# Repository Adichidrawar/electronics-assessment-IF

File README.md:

# Electronics Assessment IF

This repository contains two KiCad-based electronics design projects for an IMU and ESP32-based hardware assessment. The work is organized into two PCB design folders with schematic, layout, CSV data, and manufacturing output files.

## Project Overview

The assessment includes:
- An ESP32-oriented board design in the esp32_project folder
- A second IMU-focused board design in the imu_design folder
- Generated Gerber files for fabrication review
- Project metadata and design exports for documentation and handoff
- The solution for Part 2 — Analog front end is provided in the PDF named Part 2 — Analog front end SOLUTIONS.pdf

## Repository Structure

```text
.
├── README.md
├── esp32_project/
│   ├── esp32_project.kicad_pro
│   ├── esp32_project.kicad_sch
│   ├── esp32_project.kicad_pcb
│   ├── ESP_For_IMU.csv
│   ├── freerouting.dsn
│   ├── Gerber_files/
│   └── report.txt
└── imu_design/
    ├── imu_design.kicad_pro
    ├── imu_design.kicad_sch
    ├── imu_design.kicad_pcb
    ├── ESP_For_IMU.csv
    ├── gerber_files/
    └── imu_design.pdf
```

## Architecture and block diagram

A simple view of the intended system is:

```text
IMU sensor board ---> 300 mm cable ---> ESP32 host board ---> USB/serial or wireless link
      |                                |
      |                                +--> debug UART / status LEDs
      +--> power and ground return ---+
```

The architecture is intentionally simple:
1. The IMU board collects motion data from the sensor.
2. That data is transferred to the ESP32 board over a short, controlled digital link.
3. The ESP32 board handles communication, buffering, and any downstream logging or wireless transmission.
4. The cable carries only the signals needed for reliable timing and low-noise transfer: power, ground, clock, chip-select, data in/out, and optionally an interrupt line.

## What crosses the 300 mm cable

I would keep the cable as a compact, low-noise digital link rather than trying to carry analog signals over a long run. In practice, the following would cross the 300 mm cable:
- 3.3 V power and ground
- SPI signals: SCLK, MOSI, MISO, CS
- Optionally an interrupt or data-ready line from the IMU to the host

Using SPI is the most practical choice because it is synchronous, relatively simple to debug, and is well suited to IMU register reads and burst transfers. I would not try to carry analog outputs or high-speed clocks over this cable unless the wiring is tightly controlled and shielded.

For a 300 mm cable, I would trust roughly 4 MHz SPI as a sensible starting point. 8 MHz is possible with good layout, controlled impedance, and proper grounding, but it is a stretch for a generic cable assembly. I would prefer 2 to 4 MHz for the first prototype and only raise it after validating signal integrity.

## How I would timestamp IMU samples

I would timestamp samples on the ESP32 side using a free-running hardware timer with microsecond resolution. The approach would be:
- Capture the current timer value immediately after the IMU interrupt or after the SPI transaction completes.
- Store that timestamp together with the received sample data.
- If possible, use the IMU data-ready interrupt to latch the time at the source rather than relying on a later software poll.

For a first-pass implementation, I would expect timing error on the order of tens of microseconds, roughly 10 to 50 microseconds, depending on SPI latency, interrupt handling, and scheduler jitter. That is usually good enough for slow-motion IMU logging, but it would not be suitable for very high-rate control loops without more careful real-time design.

## Component choices

The main parts would be:
- ESP32-WROOM-32 or similar ESP32 module: the main compute and communications hub, with enough GPIO and SPI capability for the IMU link.
- A 6-axis or 9-axis IMU such as ICM-42688 or MPU-6050: provides the motion sensing and a straightforward digital interface.
- A 3.3 V low-dropout regulator: keeps the logic rail stable and clean for the sensor and the ESP32.
- Decoupling capacitors and a small reset/boot network: these are essential for reliable startup and noise immunity.
- ESD and filtering parts on the cable side: helpful for protecting the board and reducing transient noise when the cable is moved or connected.

## Rough power budget

A realistic rough budget for a simple prototype is:
- ESP32 active: about 200 to 300 mA at 3.3 V
- IMU sensor: about 1 to 3 mA
- LDO and small support circuitry: a few milliamps

That gives a total active load of roughly 0.3 to 0.8 W, depending on Wi-Fi or Bluetooth activity. For a safe design margin, I would plan for a 3.3 V supply that can comfortably deliver at least 500 mA and preferably 1 A if the ESP32 is doing wireless work.

## What is most likely to be wrong

The three biggest risks on first bring-up are:
1. Cable or connector integrity: a poor ground return, bad pinout, or marginal connector contact can make SPI look flaky.
2. Power integrity: the 3.3 V rail may dip during startup or wireless bursts, causing resets or failed sensor reads.
3. Timing and signal quality: the IMU may fail to read correctly if the SPI clock is too fast or if the bus is not cleanly routed.

When the boards arrive, I would test in this order:
- Check the 3.3 V rail at the IMU and ESP32 pins under load.
- Verify continuity and ground return between the boards.
- Perform a simple SPI register read from the IMU using a known register value and confirm the response.
- Only then move to higher-rate logging or wireless transmit tests.

## What was not finished

The current design is a good starting point, but it is not yet a fully finished hardware package. The main unfinished items are:
- A formal BOM with exact part numbers and package sizes
- More careful connector and cable pinout documentation
- A bring-up checklist and test points for fast debugging

With another 3 hours, I would focus on:
- Completing the BOM and part references
- Adding test points for power, reset, SPI, and the IMU interrupt
- Writing a simple boot-and-read procedure so the first board bring-up is fast and repeatable

## How to open the designs

1. Install KiCad on your system.
2. Open the desired project folder.
3. Open the .kicad_pro file to load the full project in KiCad.
4. Review the schematic, PCB layout, and generated Gerber outputs.

## Notes

- The project folders already contain generated manufacturing outputs, making them suitable for review or fabrication preparation.
- The repository is intended for hardware design assessment documentation and version control of the PCB work.
- The report.txt file in the ESP32 project folder can be expanded with design notes, test results, or manufacturing comments as needed.

## Author

This repository was prepared as part of the electronics assessment for the IF hardware/mechatronics take-home task.

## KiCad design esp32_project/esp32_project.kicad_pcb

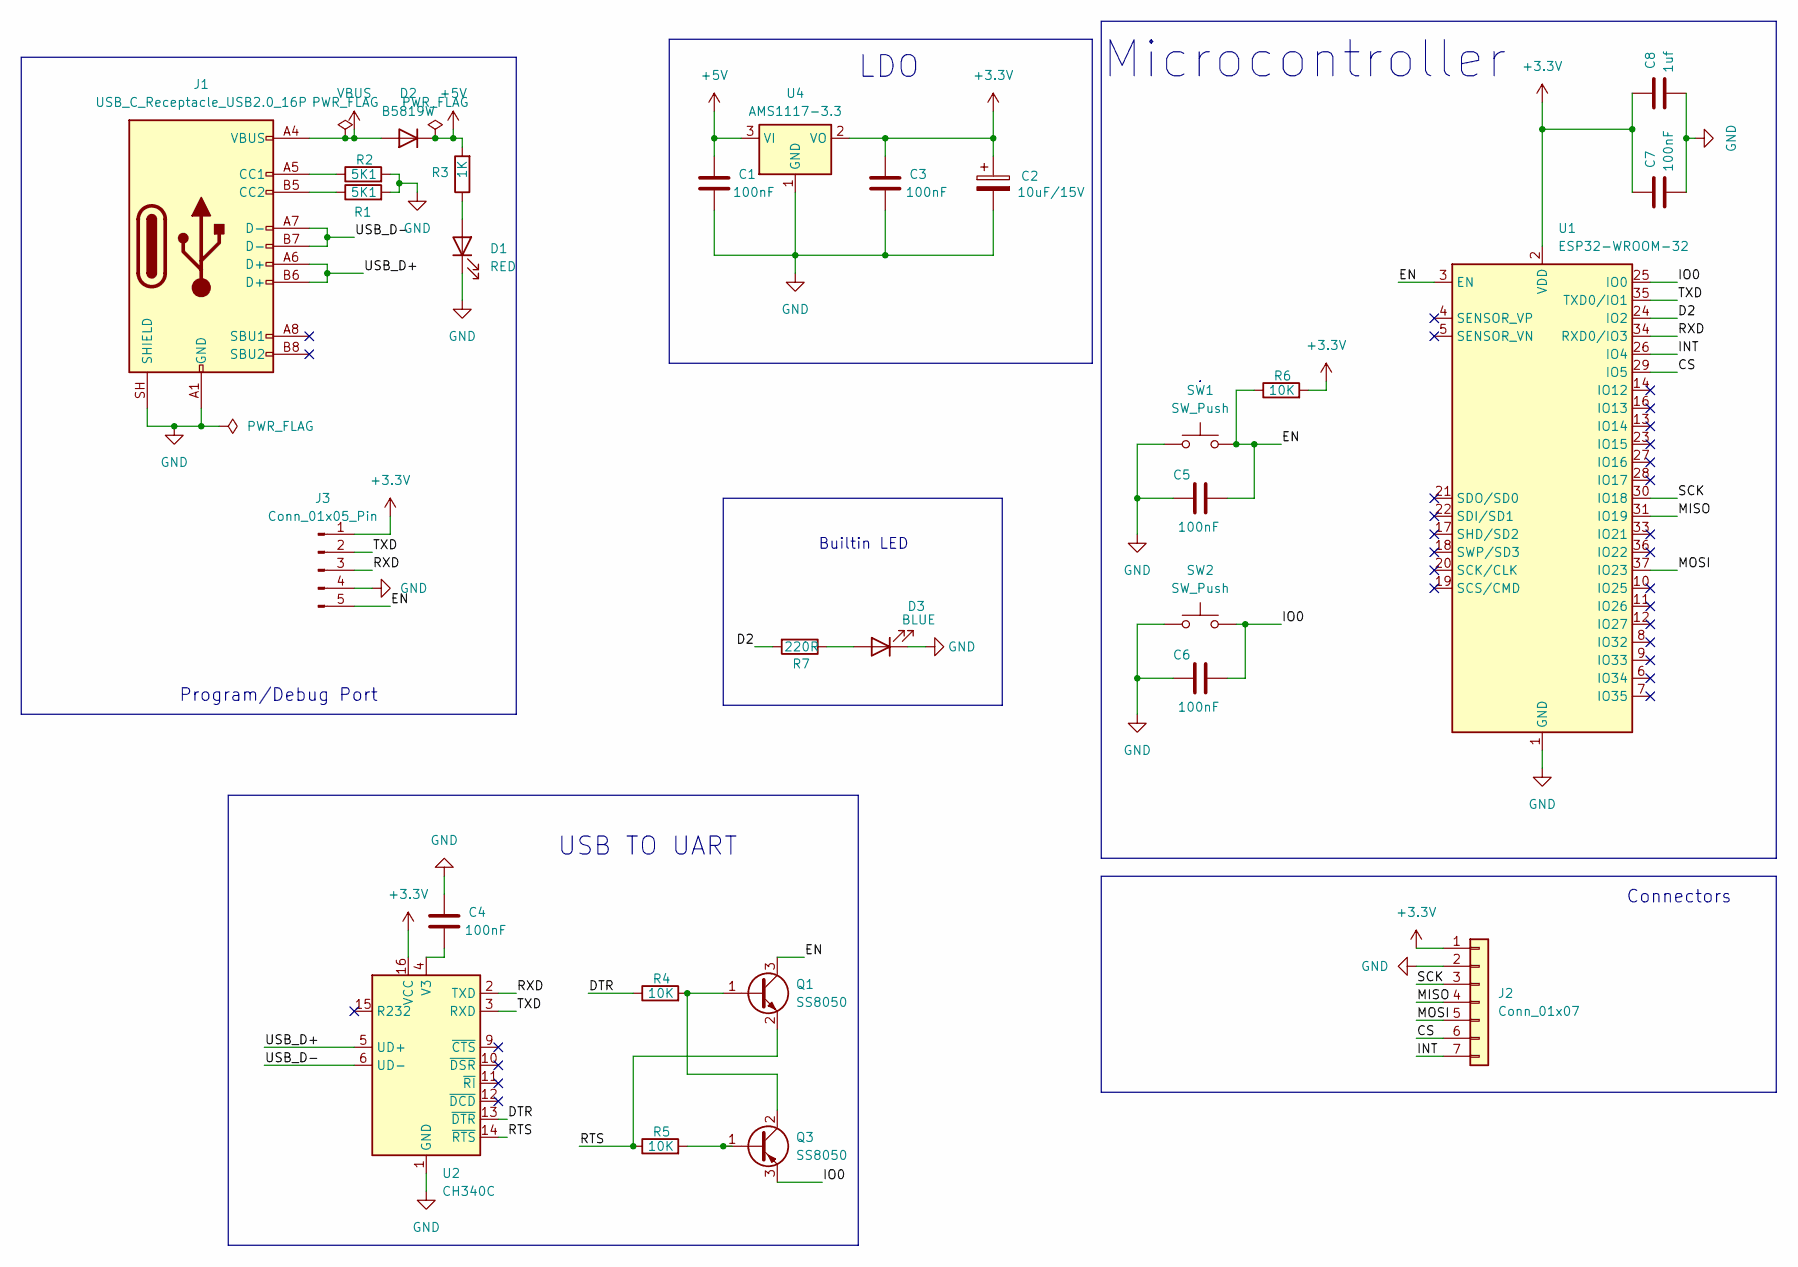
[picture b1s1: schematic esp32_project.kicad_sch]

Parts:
C1, C3, C4, C5, C6, C7: 100nF; C_0603_1608Metric
C2: 10uF/15V; CP_EIA-3216-10_Kemet-I_HandSolder
C8: 1uf; C_0603_1608Metric
D1: RED; LED_0603_1608Metric
D2: B5819W; D_SOD-123
D3: BLUE; LED_0603_1608Metric
J1: USB_C_Receptacle_USB2.0_16P; USB_C_Receptacle_HRO_TYPE-C-31-M-12
J2: Conn_01x07; JST_PH_B7B-PH-K_1x07_P2.00mm_Vertical
J3: Conn_01x05_Pin; PinHeader_1x06_P2.54mm_Vertical
Q1, Q3: SS8050; SOT-23
R1, R2: 5K1; R_0603_1608Metric
R3: 1K; R_0603_1608Metric
R4, R5, R6: 10K; R_0603_1608Metric
R7: 220R; R_0603_1608Metric
SW1, SW2: SW_Push; SW_Push_SPST_NO_Alps_SKRK
U1: ESP32-WROOM-32
U2: CH340C; SOIC-16_3.9x9.9mm_P1.27mm
U4: AMS1117-3.3; SOT-223-3_TabPin2

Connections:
+3.3V: C2.1, C3.1, C7.1, C8.1, J2.1, J3.1, R6.2, U1.2 (VDD), U2.16 (VCC), U4.2 (VO)
+5V: C1.1, D2.1 (K), R3.2, U4.3 (VI)
/CS: J2.6, U1.29 (IO5)
/D2: R7.2, U1.24 (IO2)
/DTR: R4.1, U2.13 (~DTR)
/EN: C5.2, J3.5, Q1.3 (C), R6.1, SW1.2, U1.3 (EN)
/INT: J2.7, U1.26 (IO4)
/IO0: C6.2, Q3.3 (E), SW2.2, U1.25 (IO0)
/MISO: J2.4, U1.31 (IO19)
/MOSI: J2.5, U1.37 (IO23)
/RTS: Q1.2 (E), R5.1, U2.14 (~RTS)
/RXD: J3.3, U1.34 (RXD0/IO3), U2.2 (TXD)
/SCK: J2.3, U1.30 (IO18)
/TXD: J3.2, U1.35 (TXD0/IO1), U2.3 (RXD)
/USB_D+: J1.A6 (D+), J1.B6 (D+), U2.5 (UD+)
/USB_D-: J1.A7 (D-), J1.B7 (D-), U2.6 (UD-)
GND: C1.2, C2.2, C3.2, C4.1, C5.1, C6.1, C7.2, C8.2, D1.1 (K), D3.1 (K), J1.A1 (GND), J1.A12 (GND), J1.B1 (GND), J1.B12 (GND), J1.SH (SHIELD), J2.2, J3.4, R1.2, R2.2, SW1.1, SW2.1, U1.1 (GND), U1.15 (GND), U1.38 (GND), U1.39 (GND), U2.1 (GND), U4.1 (GND)
unnamed: D1.2 (A), R3.1
unnamed: D3.2 (A), R7.1
unnamed: J1.A5 (CC1), R2.1
unnamed: J1.B5 (CC2), R1.1
unnamed: Q1.1 (B), Q3.2 (C), R4.2
unnamed: Q3.1 (B), R5.2
unnamed: C4.2, U2.4 (V3)
VBUS: D2.2 (A), J1.A4 (VBUS), J1.A9 (VBUS), J1.B4 (VBUS), J1.B9 (VBUS)

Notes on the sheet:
USB TO UART
Program/Debug Port
LDO
Microcontroller
Connectors
Builtin LED

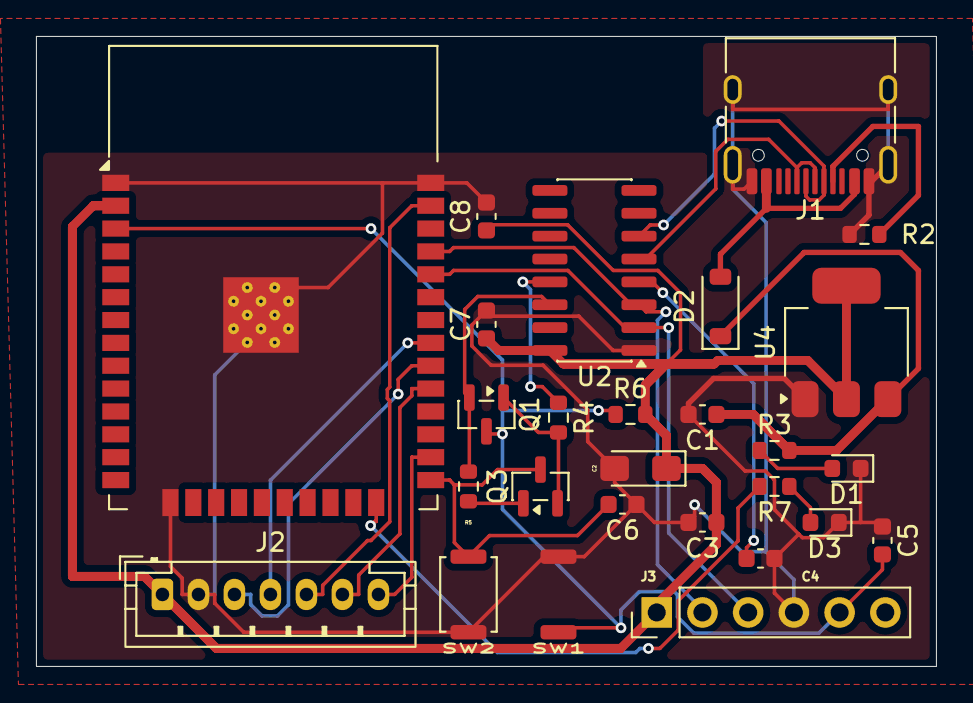
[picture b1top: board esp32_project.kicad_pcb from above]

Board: 2 copper layers, 50.0 x 35.0 mm, 27 parts (0 on the bottom side), 24 nets.

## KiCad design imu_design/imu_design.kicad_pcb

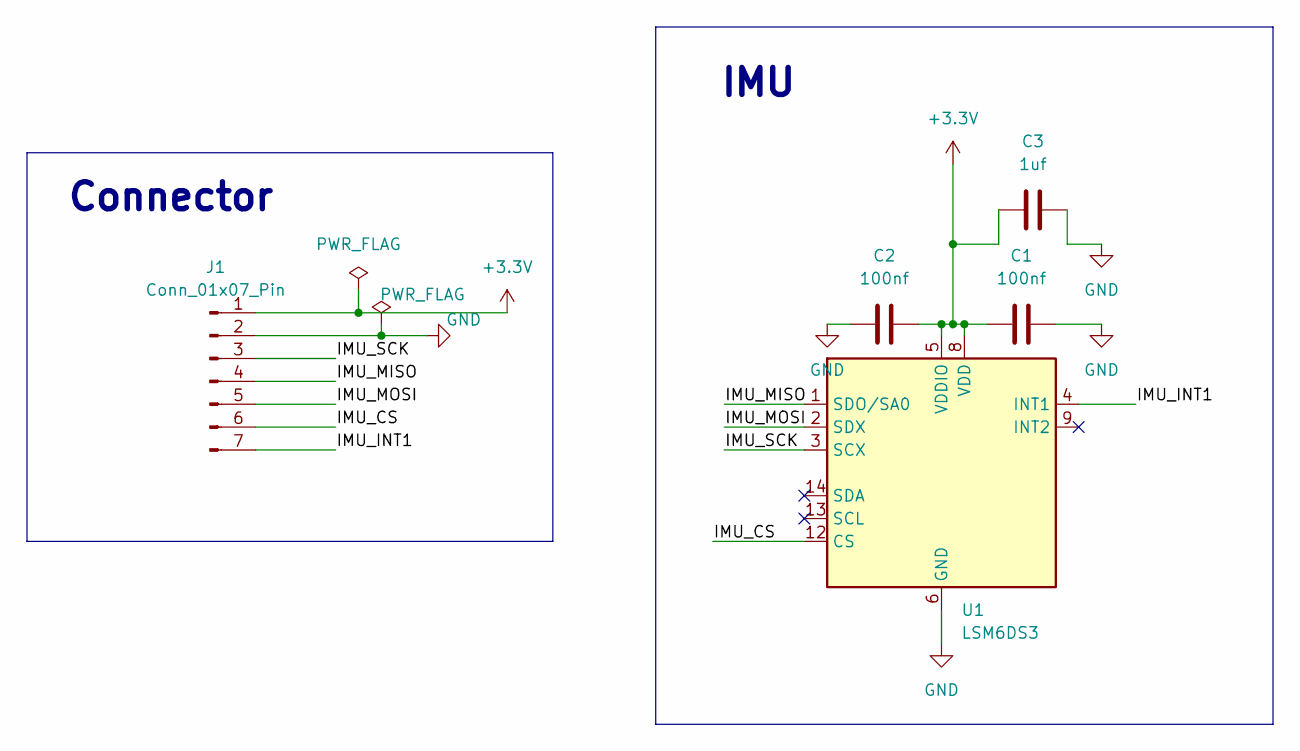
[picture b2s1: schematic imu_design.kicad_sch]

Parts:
C1, C2: 100nf; C_0603_1608Metric
C3: 1uf; C_0603_1608Metric
J1: Conn_01x07_Pin; JST_PH_B7B-PH-K_1x07_P2.00mm_Vertical
U1: LSM6DS3; LGA-14_3x2.5mm_P0.5mm_LayoutBorder3x4y

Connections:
+3.3V: C1.1, C2.2, C3.1, J1.1, U1.5 (VDDIO), U1.8 (VDD)
/IMU_CS: J1.6, U1.12 (CS)
/IMU_INT1: J1.7, U1.4 (INT1)
/IMU_MISO: J1.4, U1.1 (SDO/SA0)
/IMU_MOSI: J1.5, U1.2 (SDX)
/IMU_SCK: J1.3, U1.3 (SCX)
GND: C1.2, C2.1, C3.2, J1.2, U1.6 (GND), U1.7 (GND)

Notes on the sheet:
Connector
IMU

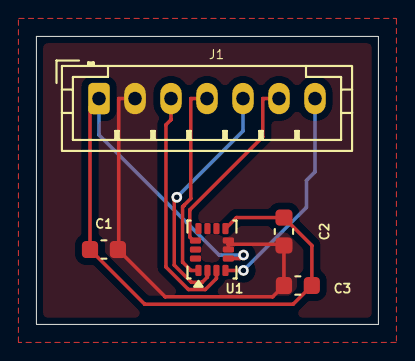
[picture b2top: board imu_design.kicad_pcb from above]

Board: 2 copper layers, 19.0 x 16.0 mm, 5 parts (0 on the bottom side), 7 nets.
